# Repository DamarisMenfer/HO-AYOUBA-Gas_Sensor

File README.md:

# MICRO-CONTROLEURS ET OPEN-SOURCE HARDWARE - Capteur de gaz et communication LoRa - Shield Arduino
Ce projet a été réalisé dans le cadre de l'enseignement "Microcontrolleurs et Open-Source Hardware" de la 5e année "Innovative Smart Systems" à l'INSA de Toulouse. 

Le projet à été realisé par AYOUBA Gael et HO Fabian, Etudiants en Informatique et Réseaux au sein du département du GEI.

# Objectif
L'objectif de ce projet est de concevoir un circuit imprimé complet (PCB). 
Le circuit est ensuite utilisé avec une carte Arduino et  une puce LoRa. 
Les données récoltées seront envoyées via le protocole LoRa sur la plateforme TTN (The Things Network).

# Equipement
- Shield Capteur de gaz

- Arduino uno 	

- Module LoRa RN2483 breakout

# Fonctionnalités
- Capteur de gas avec le branchement (Nécessitant la réalisation en salle blanche)
- Circuit d’adaptation du capteur de gaz vers l’ADC de l’Arduino UNO :
  - Filtrage des bruits contenant 2 filtres passifs et un filtre actif avec l'AOP LTC1050
  - Filtrage anti-repliement pour realiser l'echantillonage de l'ADC
- Adaptation du calibre
 
# Contenus
Ce projet contient le code source et les fichiers de conception:

- La partie schématique, décrivant le circuit électronique implémenté (composants, routage des pins)
- La partie layout, décrivant la forme de la carte, l’emplacement des différents éléments sur celle-ci et la trajectoire des pistes de routage ainsi qu'une partie 3D.
- Code arduino pour LoRa

# Schemas PCB
Conception du schematic :

Voici plusieurs fonctionnalités du schema:

- La résistance d'entrée (R1) est une resistance de protection, elle protège l'amplificateur opérationnel des décharges électrostatiques. De plus celle ci est associée au condensateur C1 pour filtrer le bruit de tension.
- Le circuit entre le condensateur C1 et la résistance R2 nous permet de filtrer le bruit de courant.
- La résistance R3 est utilisée pour adapter notre montage au calibre correct. La resistance R3 peut être modifiée afin de mieux calibrer le montage.
- Nous avons mis en place un filtre actif grace au circuit entre le condensateur C2 et la resistance R4 en sortie de l'amplificateur.
- la résistance R5 et le condensateur C4 constituent un filtre passe-bas en sortie de l'ensemble.
- Enfin, le condensateur C3 filtre le bruit provenant de l’entrée de tension 5V.

# PCB footprint sur KiCad
Conception du Layout:

Afin de realiser le footprint correctement, nous avons mis en pratique les points suivants:
- Nous avons choisi une largeur de piste de 0.8 mm, afin que notre constructeur puisse le réaliser avec son équipement.
- Nous avons decidé d'inserer uniquement la connectique de la plaque RN2483 Breakout afin d'optimiser l'espace du footprint. D'autant plus que nous considerons que la carte RN2483 ne sera pas directement integrée sur le shield mais reliée par des fils (connecteur).
- Nous avons utilisé une couche de GND au verso de la plaque nous permettant d'optimiser encore plus notre espace en réduisant le nombre de connections.

Comme le montre l'image ci-dessus, il s'agit d'un tracé sur une seule face. 
# PCB 3D view
Vision 3D:
Vous pouvez voir ci-dessous une représentation 3D de notre conception. 
Le choix des composant a été réalisé sous la condition qu'ils soient traversants et le plus petit possible.

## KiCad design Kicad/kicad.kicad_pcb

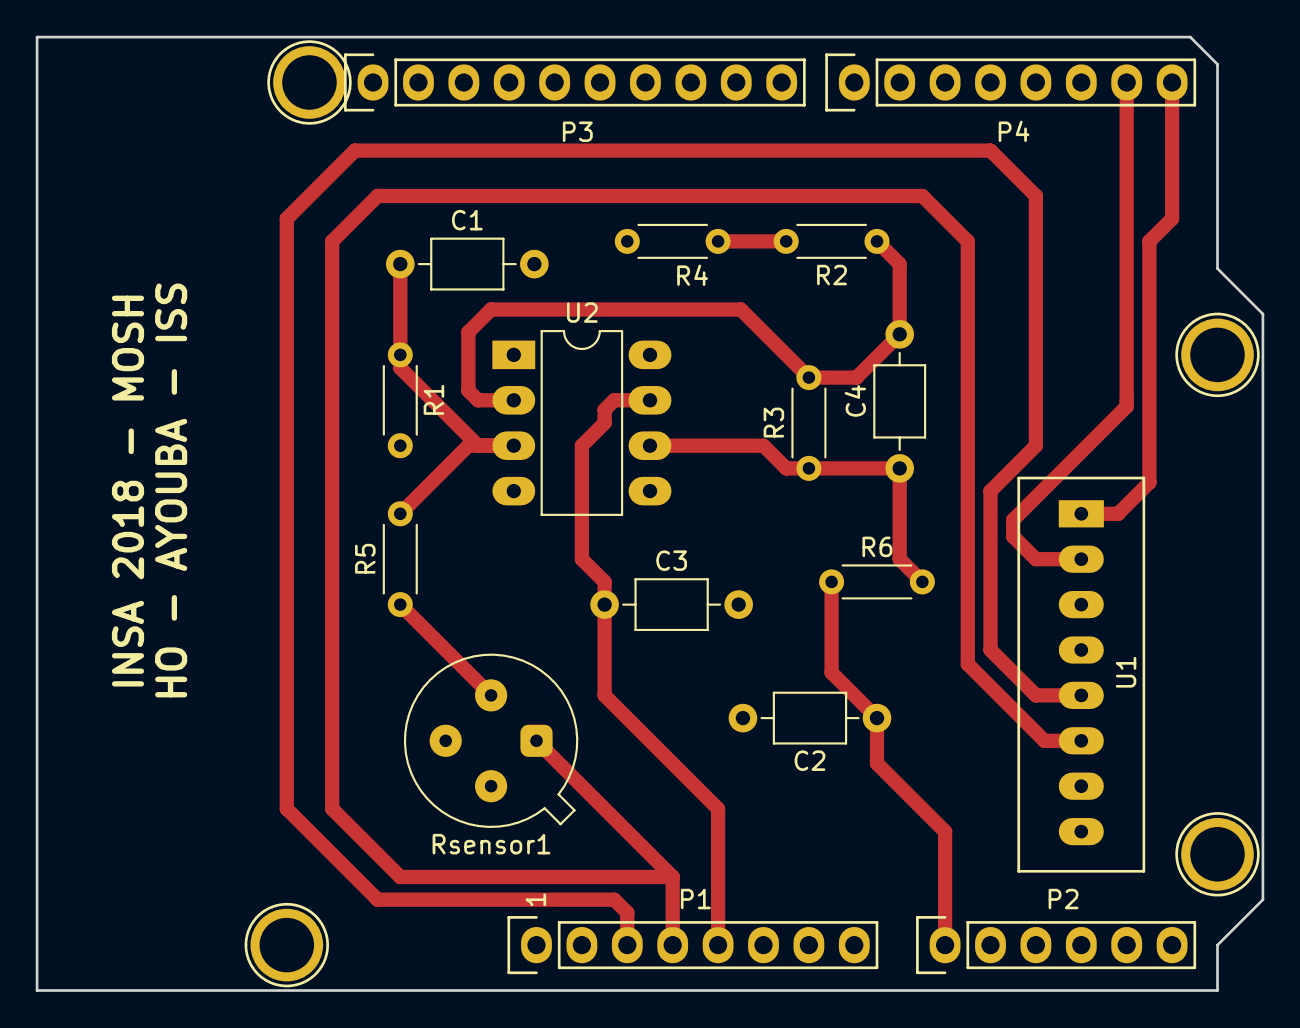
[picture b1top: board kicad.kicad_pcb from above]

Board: 2 copper layers, 68.6 x 53.3 mm, 21 parts (0 on the bottom side), 12 nets.

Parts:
C1, C2, C3: 100n; C_Axial_L3.8mm_D2.6mm_P7.50mm_Horizontal
C4: 1u; C_Axial_L3.8mm_D2.6mm_P7.50mm_Horizontal
P1: Power; Socket_Strip_Arduino_1x08
P2: Analog; Socket_Strip_Arduino_1x06
P3: Digital; Socket_Strip_Arduino_1x10
P4: Digital; Socket_Strip_Arduino_1x08
P5, P6, P7, P8: CONN_01X01; Arduino_1pin
R1, R3: 100k; R_Axial_DIN0204_L3.6mm_D1.6mm_P5.08mm_Horizontal
R2, R6: 1k; R_Axial_DIN0204_L3.6mm_D1.6mm_P5.08mm_Horizontal
R4: 220; R_Axial_DIN0204_L3.6mm_D1.6mm_P5.08mm_Horizontal
R5: 10k; R_Axial_DIN0204_L3.6mm_D1.6mm_P5.08mm_Horizontal
Rsensor1: R; TO-5-4
U1: RN2483Breakout; Module_RN2483_Breakout
U2: LTC1050; DIP-8_W7.62mm_LongPads

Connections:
+3V3: P1.4, Rsensor1.1, U1.6
+5V: C3.1, P1.5, U2.7
/A0: C2.1, P2.1, R6.1
/Reset: P1.3, U1.5
/Rx: P4.8, U1.1
/Tx: P4.7, U1.2
GND: C1.2, C2.2, C3.2, P1.6, P1.7, P3.4, R1.2, R4.2, U1.8, U2.4
unnamed: C1.1, R1.1, R5.2, U2.3
unnamed: C4.1, R3.1, R6.2, U2.6
unnamed: C4.2, R2.1, R3.2, U2.2
unnamed: R2.2, R4.1
unnamed: R5.1, Rsensor1.2

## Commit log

2018-11-29 Create Kicad
2018-11-29 Create ll
2018-11-29 Create f
